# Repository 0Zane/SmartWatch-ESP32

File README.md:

# ESP32 Smartwatch Project

## Project Goals
Build a custom wearable smart watch from scratch to explore embedded systems, firmware developpement, and PCB integration. 

## Ideas for Hardware Architecture

### Processing & Display
* **MCU:** ESP32-S3-WROOM-1 for Wi-Fi/BLE and dual-core processing.
* **Display:** 1.28" TFT LCD via SPI.
* **Input:** 3x Physical buttons .

### Sensors
* **Timekeeping:** Still looking for a compact RTC module
* **ToF Ranging:** VL53L0X (I2C) for distance measurement up to 2m via infrared pulses.
* **Biometrics:** MAX30102 for Heart Rate (requires tight skin contact).
* **Motion:** Still looking for gyroscope / accelerometer if required for the project.
* **Utility:** IR TX + IR RX

### Power Management
* **Battery:** LiPo (around 500mAh.
* **Charging:** Still looking for power management module.

## Software Features
* **Firmware:** Written in C++ via PlatformIO.
* **Power Management:** Sleep mode implementation with external wake-up interrupts.
* **Connectivity:**
    * Wi-Fi/BLE scanning ans testing tools.
    * ESP-NOW for ultra-fast communication with other ESP devices.

## Development Stages
1. **Prototyping:** Wiring all modules on breadboard with an ESP32 DevKit.
2. **Schematic & PCB :** I will use KiCAD to design PCB and schematics
4. **Assembly:** Probably hand soldering.
5. **Case creation  :** I will learn to use 3d modeling CAD like Fusion360 to create a case for the project.

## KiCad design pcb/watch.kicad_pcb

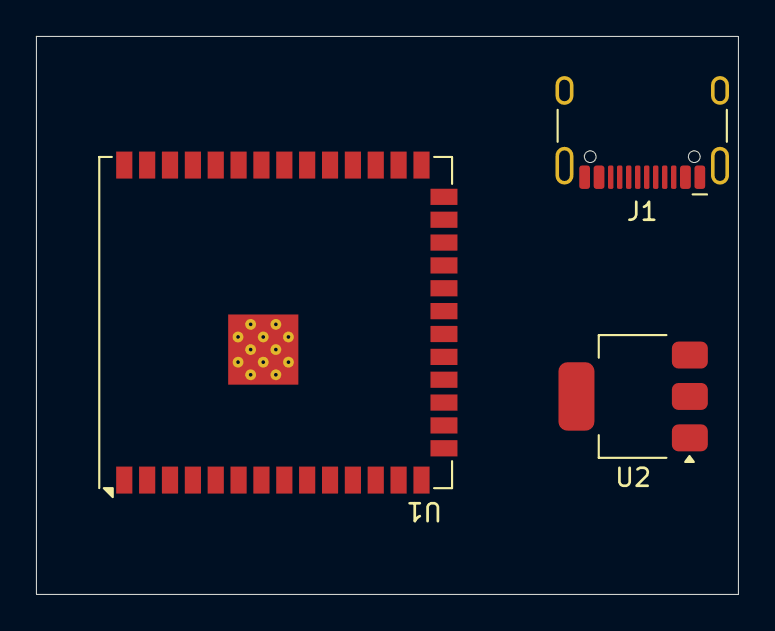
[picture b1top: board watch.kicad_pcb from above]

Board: 2 copper layers, 39.0 x 31.0 mm, 3 parts (0 on the bottom side), 5 nets, no tracks yet.

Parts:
J1: USB_C_Receptacle_USB2.0_16P; USB_C_Receptacle_HCTL_HC-TYPE-C-16P-01A
U1: ESP32-S3-WROOM-1; ESP32-S3-WROOM-1U
U2: AMS1117-3.3; SOT-223-3_TabPin2

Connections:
+3V3: U1.2 (3V3), U2.2 (VO)
+5V: J1.A4 (VBUS), J1.A9 (VBUS), J1.B4 (VBUS), J1.B9 (VBUS), U2.3 (VI)
GND: J1.A1 (GND), J1.A12 (GND), J1.B1 (GND), J1.B12 (GND), J1.SH (SHIELD), U1.1 (GND), U1.40 (GND), U1.41 (GND), U2.1 (GND)
USB_DATA+: J1.A6 (D+), J1.B6 (D+)
USB_DATA-: J1.A7 (D-), J1.B7 (D-)

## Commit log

2026-01-13 Adding first schematic
    I chose ESP32-S3-WROOM-1 NR16R8, and started the schematic.
2026-01-13 Building platform IO environment
2026-01-13 Removing schematic duplicate
2026-01-13 Adding TFT library to the project
2026-01-13 Update README with project details for ESP32 smartwatch
    Added detailed project goals, hardware architecture, software features, and development stages for the ESP32 smartwatch project.
2026-01-13 Fix formatting and spelling in README.md
    Corrected formatting and spelling in README.
2026-01-13 Refine README.md sensor and software feature details
    Updated sensor and software feature descriptions for clarity.
2026-01-14 Displaying something on Screen
2026-01-15 First UI (not interactive)
2026-01-16 Adding different pages
2026-01-17 Adding serial monitor
2026-01-17 Adding button detection
2026-01-18 fixung rebounding button error
2026-01-18 Fixing bugs when going past the number of pages + upgrading to better UI
2026-01-18 Rename section from 'Hardware Architecture' to 'Ideas for Hardware Architecture'
2026-01-18 Adding buttons (still draft)
2026-01-18 Adding image
2026-01-19 Holding button allows to navigate through pages.
2026-01-20 Update hardware architecture details in README
    Correct MCU description and update battery and charging details.
2026-01-20 Add BSELECT constant for button pin
    Added a new constant for BSELECT button pin.
2026-01-28 Not verified structure update
2026-01-30 deleting kicad PCB
2026-01-30 adding arduino extension
2026-01-30 Commenting the todo list
2026-02-05 Updating UI
2026-02-05 Updating boot page
2026-02-05 Turning button detection to pullup
2026-02-07 Correcting index
2026-02-07 Adding rectangle on screen
2026-02-07 Tool to calculate the pixel lenght of a string
2026-02-07 Replacing a coordonate for text
2026-02-08 small fixes in screen refreshess
2026-02-13 Changing board to ESP32-S3 -N16R8
2026-02-16 Creating header structure
2026-04-03 Creating PCB project
2026-04-03 Placing ESP32-S3-WROOM-1
2026-04-03 Updating .gitignore for PCB editing
2026-04-04 Adding USBC schematic
2026-04-04 Placing elements on PCB cut layer
2026-04-04 .kicad_pro update
2026-04-06 Adding AMS1117
2026-04-06 Ignoring every local KiCad custom files
2026-04-06 Placing the PCB correctly, replacing ESP32-S3-WROOM-1 by ESP32-S3-WROOM-1U, placing AMS1117
